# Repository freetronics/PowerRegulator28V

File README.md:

Freetronics Power-over-Ethernet 28V Regulator
=============================================
Copyright 2011 Freetronics Pty Ltd  
Freetronics site:  <www.freetronics.com>  
Freetronics email: <info@freetronics.com>  

Module to regulate power supplied on Power-over-Ethernet connection
down to 7Vdc for supply to the on-board voltage regulator in an
Arduino Uno, Freetronics Eleven, or other compatible board
using the Freetronics Ethernet Shield.

Features:

 * Adds Power-over-Ethernet "PD" (powered device) support to the
   Freetronics Ethernet shield.
 * Input voltage range 9-28Vdc.
 * Output voltage limited to 7V and fed to Arduino on-board voltage
   regulator via Ethernet shield for further regulation down to 5V.
 * Input protection diode to prevent damage due to reverse polarity.
 * Plugs directly onto Freetronics Ethernet Shield.
 * "Power on" LED.

More information is available at:

  http://www.freetronics.com/poe-regulator-28v

The "docs" folder within this repository includes a handy copy of the
schematic in PDF format and image(s) of the pcb.

INSTALLATION
------------
The design is saved as an EAGLE project. EAGLE PCB design software is
available from www.cadsoftusa.com free for non-commercial use. To use
this project download it and place the directory containing these files
into the "eagle" directory on your computer. Then open EAGLE and
navigate to Projects -> eagle -> PoERegulator28V.

DISTRIBUTION
------------
The specific terms of distribution of this project are governed by the
license referenced below.

LICENSE
-------
Licensed under the TAPR Open Hardware License (www.tapr.org/OHL).
The "license" folder within this repository also contains a copy of
this license in plain text format.

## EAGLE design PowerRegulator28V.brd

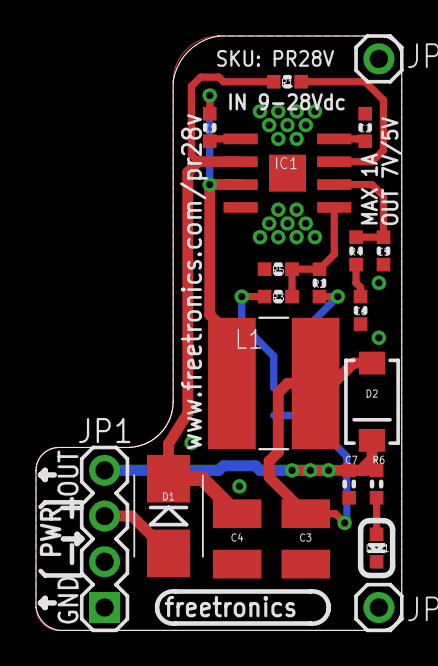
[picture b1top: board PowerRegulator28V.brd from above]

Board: 2 copper layers, 20.3 x 33.0 mm, 22 parts (1 on the bottom side), 14 nets.

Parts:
C1: 10nF 50V; 0603
C2: 100nF; 0603
C3: 22uF 10V 1210 ceramic; C1210
C4: 10uF 50V 1210 ceramic; C1210
C5: 22pF NOT PLACED; 0603
C6: 2.2nF 0603; 0603
C7: 1uF 16V; 0603
D1: SS16 SCHOTTKY SMA; SMA-SMB-DIODE
D2: SK34A-LTP 3A 40V SCHOTTKY; SMA-DIODE
IC1: EUP3476SO08T; SO08T
JP1: Pwr Header; 1X04
JP2, JP3: 1X01
L1: CDRH6D38SMT; CDRH
LED1: BLUE; LED-0603
R1: 100K 0603; 0603
R2: 82.5K 1% 0603; 0603
R3: 187K 1% 0603; 0603
R4: 15K 0603; 0603
R5: 10K 1% 0603; 0603
R6: 1K; 0603
SJ1: 5VSEL; SJ

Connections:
GND: C2.1, C3.2, C4.2, C5.2, C6.2, C7.2, IC1.4, IC1.9, JP1.1, JP1.2, JP3.1, LED1.C, R5.1
unnamed: R3.1, SJ1.1
unnamed: IC1.7, R1.1
unnamed: IC1.5, R2.2, R3.2, R5.2
unnamed: C5.1, IC1.6, R4.2
unnamed: C6.1, R4.1
unnamed: C1.2, IC1.1
unnamed: C2.2, IC1.8
unnamed: C1.1, IC1.3, L1.1
unnamed: LED1.A, R6.2
POS: D1.A, JP1.3
VFEED: C3.1, D2.A, L1.2, R2.1, SJ1.2
VIN: C4.1, D1.C, IC1.2, R1.2
VOUT: C7.1, D2.C, JP1.4, R6.1

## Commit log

2011-08-19 Initial import
2011-08-22 Routing
2011-08-24 Updated reg footprint
2011-08-25 Updated footprints for caps and inductor
2011-08-26 General cleanups
2011-08-28 Schematic notes and routing
2011-08-28 Updated inductor overlay and product URL
2011-08-28 Updated schematic labels and resistor values
2011-08-29 Updated SO8 package
2011-09-07 Minor routing and schematic changes
2011-09-07 Renamed project files
2011-09-07 Added preview images
2011-09-07 Fixed silkscreen label
2011-09-30 Playing with output protection tweaks
2011-10-13 v1.0 release
2011-10-26 v1.1 production release
2011-12-12 Schematic and Reference PDF renamed
2019-04-24 Designator improvement

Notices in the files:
PowerRegulator28V.brd:
(c) 2011 Freetronics Pty Ltd
